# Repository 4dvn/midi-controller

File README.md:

# midi-controller
MIDI over USB project using buttons, sliders and potentiometers, based on a the ATmega32u4

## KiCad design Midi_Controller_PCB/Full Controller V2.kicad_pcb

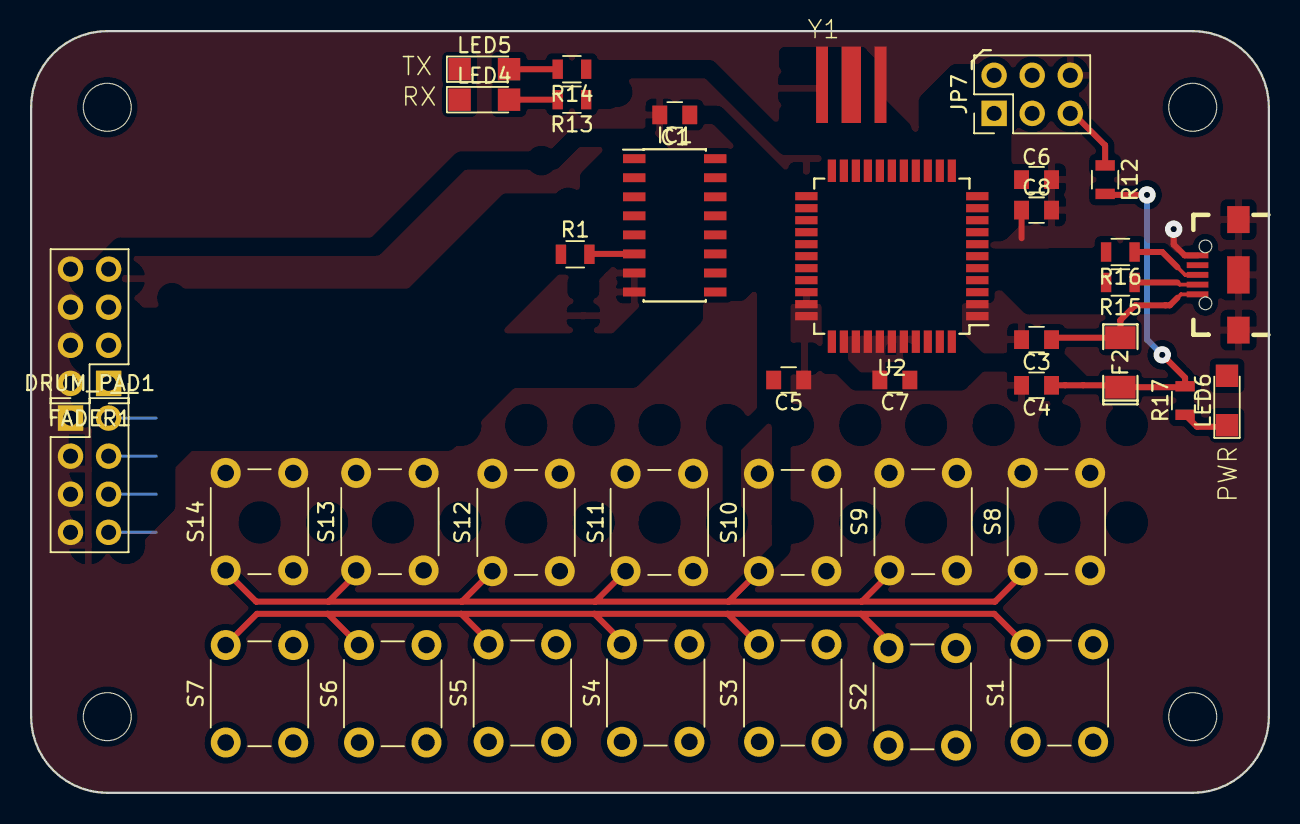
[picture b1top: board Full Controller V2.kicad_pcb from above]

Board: 2 copper layers, 82.6 x 50.8 mm, 56 parts (0 on the bottom side), 42 nets.

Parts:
C1, C2, C5, C7: 0.1uF; C_0805
C3, C4, C6, C8: 1uF; C_0805
D1, D2, D3, D4, D5, D6, D7: BAS40-06; SOT-23
DRUM_PAD1: PINHD-2X4; Pin_Header_Straight_2x04_Pitch2.54mm
F2: 500ma; SMD-1206_Pol
FADER1: PINHD-2X4; Pin_Header_Straight_2x04_Pitch2.54mm
H1, H2, H3, H4: MOUNT-HOLE3.2; MountingHole_3.2mm_M3
IC1: 4051D; SOIC-16_3.9x9.9mm_Pitch1.27mm
IC2: 74LS595D; SOIC-16_3.9x9.9mm_Pitch1.27mm
J2: USB MINI B; USB-B-MICRO-SMD
JP7: ICSP HEADER; Pin_Header_Straight_2x03_Pitch2.54mm
LED4: RX; LED_1206
LED5: TX; LED_1206
LED6: POWER; LED_1206
R1, R12: 10K; R_0805
R2, R3, R4, R5: 1M; R_0805
R13, R14, R17: 1K; R_0805
R15, R16: 22; R_0805
S1, S2, S3, S4, S5, S6, S7, S8, S9, S10, S11, S12, S13, S14: 10-XX; SW_PUSH_6mm
U2: 32U4; TQFP-44_10x10mm_Pitch0.8mm
Y1: AWSCR; MTD

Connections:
/A0: IC1.3, U2.36
/AREF: C7.1, U2.42
/C1: D1.3, IC2.15
/C2: D2.3, IC2.1
/C3: D3.3, IC2.2
/C4: D4.3, IC2.3
/C5: D5.3, IC2.4
/C6: D6.3, IC2.5
/C7: D7.3, IC2.6
/CLOCK: IC2.11, U2.18
/D0: S1.2, S2.2, S3.2, S4.2, S5.2, S6.2, S7.2, U2.31
/D1: S8.1, S9.1, S10.1, S11.1, S12.1, S13.1, S14.1, U2.32
/D+: R16.2, U2.4
/D-: R15.2, U2.3
/DATA: IC2.14, U2.19
/LATCH: IC2.12, U2.25
/MISO: JP7.1, U2.11
/MOSI: JP7.4, U2.10
/POT1: FADER1.1, IC1.5
/POT2: FADER1.2, IC1.4
/POT3: FADER1.3, IC1.2
/POT4: FADER1.4, IC1.1
/POT5: FADER1.5, U2.37
/POT6: FADER1.6, U2.38
/PZO1: DRUM_PAD1.2, IC1.15, R2.2
/PZO2: DRUM_PAD1.4, IC1.14, R3.2
/PZO3: DRUM_PAD1.6, IC1.13, R4.2
/PZO4: DRUM_PAD1.8, IC1.12, R5.2
/RESET: JP7.5, R12.1, U2.13
/RX_LED: R13.1, U2.8
/S0: IC1.11, U2.28
/S1: IC1.10, U2.29
/S2: IC1.9, U2.30
/SCK: JP7.3, U2.9
/TX_LED: R14.1, U2.22
GND: C1.2, C2.2, C3.2, C4.2, C5.2, C6.2, C7.2, C8.2, DRUM_PAD1.1, DRUM_PAD1.3, DRUM_PAD1.5, DRUM_PAD1.7, FADER1.7, IC1.7, IC1.8, IC2.8, IC2.13, J2.GND, J2.SHIELD1, J2.SHIELD2, J2.SHIELD3, JP7.6, R1.1, R2.1, R3.1, R4.1, R5.1, U2.5, U2.15, U2.23, U2.33, U2.35, U2.43, Y1.GND
unnamed: C8.1, U2.6
unnamed: IC1.6, R1.2
unnamed: U2.16, Y1.OUT
unnamed: U2.17, Y1.IN
UVCC: C3.1, C6.1, F2.2, J2.VBUS, U2.2, U2.7
VCC: C1.1, C2.1, C4.1, C5.1, F2.1, FADER1.8, IC1.16, IC2.10, IC2.16, JP7.2, R12.2, R17.2, U2.14, U2.24, U2.34, U2.44

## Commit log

2019-02-10 Initial Upload
